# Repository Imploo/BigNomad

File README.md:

# BigNomad Keyboard

The BigNomad is a 9×5 keys, column-staggered split keyboard based largely on the [Nomad Keyboard](https://github.com/fiendie/NomadKeyboard), which is based on the [Sofle Choc by Brian Low](https://github.com/brianlow/SofleKeyboard).
It uses low profile Kailh Choc v1 switches with hotswap sockets and features per-key RGB lighting via SK6812 Mini-E LEDs.
Compared to the Nomad Keyboard the BigNomad offers an additional numpad as inner columns, an extra thumb cluster key, and an additional modifier key in the 5th row.
To make the keyboard more compact, support for OLED or pro micro based mcus are dropped. Instead, the mcu must be a RP2040 mini. Added support for a rotary encoder on top of the mcu footprint as well.

## RGB setup
I wanted to be able to control all leds individually on both hands, which is not possible when synching state through a serial connection. So I connected the last led to the trrs jack. All leds can then be chained in one long chain and all leds can be individually addressed. If you don't want this behaviour, choose jumper mcu on both halves. 

One caveat with using a trrs jack this way is that the serial connection is limited to half duplex serial. No full duplex or i2c possible. But since its not neccesary to sync the led state to the slave, the half duplex serial is fast enough.

## Bill of materials
- 2x RP2040 mini
- 6x female round header socket, the low profile ones that accept diode legs. They are break-apart into correct length, you need at least 46 pins.
- 2x EC11 rotary encoder
- 2x TRRS jack
- 1x TRRS cable
- 1x USB cable (pro tip; use the magnetic ones with data lines)
- 82x DIN123 diodes
- 82x SK6812 mini RGB leds
- 82x Kailh Choc hotswap sockets
- 82x Kailh Choc switches of your choice

## Build instructions
1. For the left hand side; Solder jumper J_RGB labeled mcu and keep trrs clear of any solder.
2. For the right hand side; choose whether you want to control the leds from the slave mcu or from the trrs plug. Solder the jumper mcu OR trrs. 
3. Solder diodes, keep an eye on the direction printed on the silk sheet.
4. Solder hotswap sockets
5. Solder RGBs
6. Solder encoder on the front side of the pcb.
7. Solder hotswap socket for mcu on the back side of the pcb. 
8. Solder pins on mcu
9. Place mcu, keep in mind the pin labeled as vcc!
10. Flash mcu and check workings of the RGB
11. Place a switch in a socket and test the matrix
12. Build the right hand side and test everything
13. Connect the two halves with a trrs cable and test the complete matrix. 

## Firmware 

Nomad uses [QMK firmware](https://qmk.fm/)

## Default layout 

TODO

## Images
These are still the original Nomad images, BigNomad images are pending..

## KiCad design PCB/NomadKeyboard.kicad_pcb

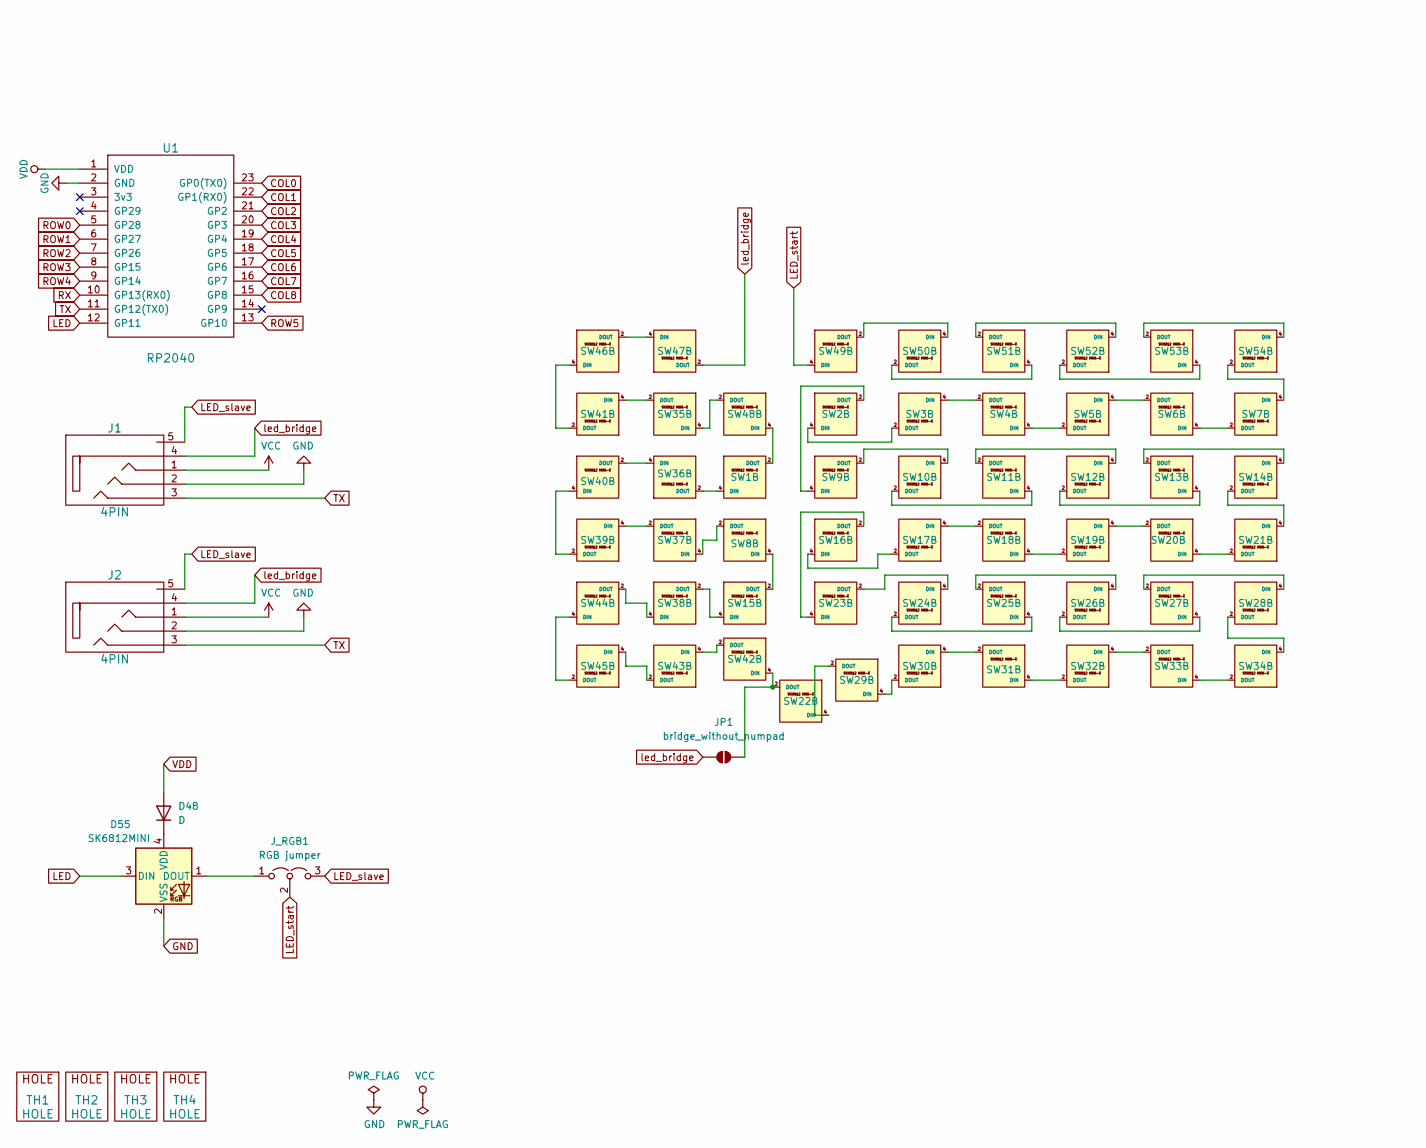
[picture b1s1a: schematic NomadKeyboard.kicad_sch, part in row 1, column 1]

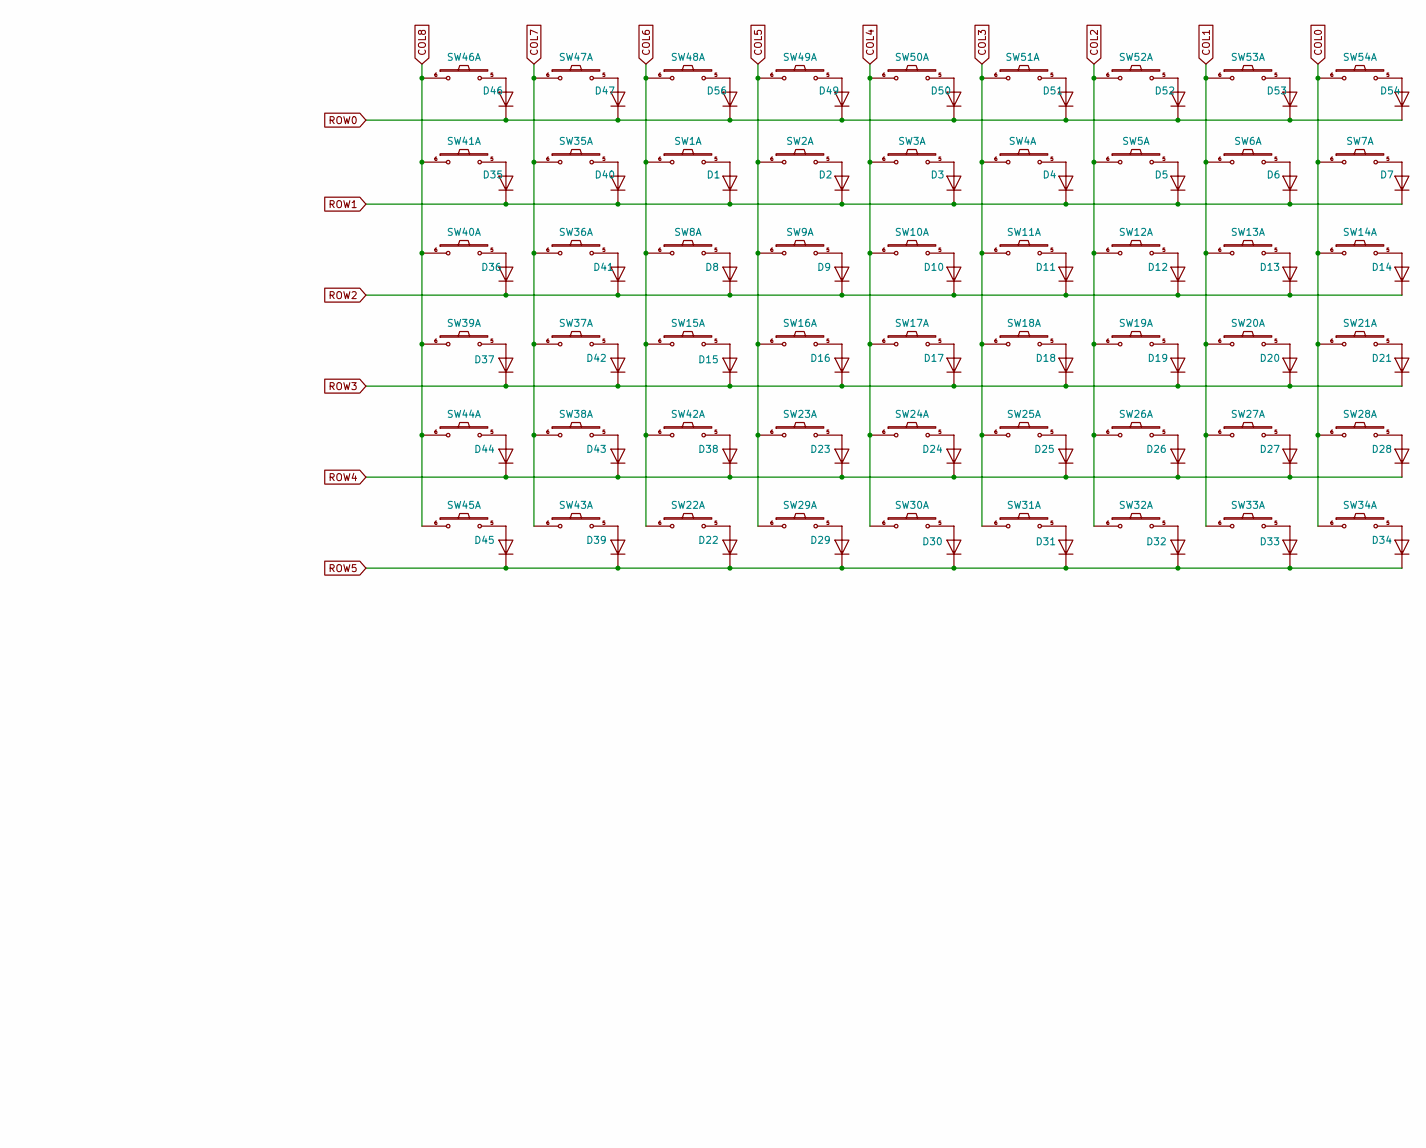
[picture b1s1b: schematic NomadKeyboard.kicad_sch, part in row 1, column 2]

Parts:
D1, D2, D3, D4, D5, D6, D7, D8, D9, D10, D11, D12, D13, D14, D15, D16, D17, D18, D19, D20, D21, D22, D23, D24, D25, D26, D27, D28, D29, D30, D31, D32, D33, D34, D35, D36, D37, D38, D39, D40, D41, D42, D43, D44, D45, D46, D47, D48, D49, D50, D51, D52, D53, D54, D56: D; crkbd-diode
D55: SK6812MINI; SK6812MiniE
J1, J2: 4PIN; MJ-4PP-9
JP1: bridge_without_numpad; SolderJumper-2_P1.3mm_Open_TrianglePad1.0x1.5mm
J_RGB1: RGB jumper; SolderJumper-3_P2.0mm_Open_TrianglePad1.0x1.5mm
SW1, SW2, SW3, SW4, SW5, SW6, SW7, SW8, SW9, SW10, SW11, SW12, SW13, SW14, SW15, SW16, SW17, SW18, SW19, SW20, SW21, SW22, SW23, SW24, SW25, SW26, SW27, SW28, SW29, SW30, SW31, SW32, SW33, SW34, SW35, SW36, SW37, SW38, SW39, SW40, SW41, SW42, SW43, SW44, SW45, SW46, SW47, SW48, SW49, SW50, SW51, SW52, SW53, SW54: SW_PUSH_LED; Choc_Hotswap_SK6812MiniE
TH1, TH2, TH3, TH4: HOLE; HOLE_M2_TH
U1: RP2040; rp2040-zero-smd

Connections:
COL0: SW7.6, SW14.6, SW21.6, SW28.6, SW34.6, SW54.6, U1.23 (GP0(TX0)); also elsewhere on the board
COL1: SW6.6, SW13.6, SW20.6, SW27.6, SW33.6, SW53.6, U1.22 (GP1(RX0)); also elsewhere on the board
COL2: SW5.6, SW12.6, SW19.6, SW26.6, SW32.6, SW52.6, U1.21 (GP2); also elsewhere on the board
COL3: SW4.6, SW11.6, SW18.6, SW25.6, SW31.6, SW51.6, U1.20 (GP3); also elsewhere on the board
COL4: SW3.6, SW10.6, SW17.6, SW24.6, SW30.6, SW50.6, U1.19 (GP4); also elsewhere on the board
COL5: SW2.6, SW9.6, SW16.6, SW23.6, SW29.6, SW49.6, U1.18 (GP5); also elsewhere on the board
COL6: SW1.6, SW8.6, SW15.6, SW22.6, SW42.6, SW48.6, U1.17 (GP6); also elsewhere on the board
COL7: SW35.6, SW36.6, SW37.6, SW38.6, SW43.6, SW47.6, U1.16 (GP7); also elsewhere on the board
COL8: SW39.6, SW40.6, SW41.6, SW44.6, SW45.6, SW46.6, U1.15 (GP8); also elsewhere on the board
GND: D55.2 (VSS), J1.2, J2.2, SW1.3 (GND), SW2.3 (GND), SW3.3 (GND), SW4.3 (GND), SW5.3 (GND), SW6.3 (GND), SW7.3 (GND), SW8.3 (GND), SW9.3 (GND), SW10.3 (GND), SW11.3 (GND), SW12.3 (GND), SW13.3 (GND), SW14.3 (GND), SW15.3 (GND), SW16.3 (GND), SW17.3 (GND), SW18.3 (GND), SW19.3 (GND), SW20.3 (GND), SW21.3 (GND), SW22.3 (GND), SW23.3 (GND), SW24.3 (GND), SW25.3 (GND), SW26.3 (GND), SW27.3 (GND), SW28.3 (GND), SW29.3 (GND), SW30.3 (GND), SW31.3 (GND), SW32.3 (GND), SW33.3 (GND), SW34.3 (GND), SW35.3 (GND), SW36.3 (GND), SW37.3 (GND), SW38.3 (GND), SW39.3 (GND), SW40.3 (GND), SW41.3 (GND), SW42.3 (GND), SW43.3 (GND), SW44.3 (GND), SW45.3 (GND), SW46.3 (GND), SW47.3 (GND), SW48.3 (GND), SW49.3 (GND), SW50.3 (GND), SW51.3 (GND), SW52.3 (GND), SW53.3 (GND), SW54.3 (GND), U1.2 (GND); also elsewhere on the board
LED: D55.3 (DIN), U1.12 (GP11); also elsewhere on the board
LED_slave: J1.5, J2.5, J_RGB1.3 (B); also elsewhere on the board
LED_start: J_RGB1.2 (C), SW49.4 (DIN); also elsewhere on the board
unnamed: D1.2 (A), SW1.5
unnamed: D2.2 (A), SW2.5
unnamed: D3.2 (A), SW3.5
unnamed: D4.2 (A), SW4.5
unnamed: D5.2 (A), SW5.5
unnamed: D6.2 (A), SW6.5
unnamed: D7.2 (A), SW7.5
unnamed: D8.2 (A), SW8.5
unnamed: D9.2 (A), SW9.5
unnamed: D10.2 (A), SW10.5
unnamed: D11.2 (A), SW11.5
unnamed: D12.2 (A), SW12.5
unnamed: D13.2 (A), SW13.5
unnamed: D14.2 (A), SW14.5
unnamed: D15.2 (A), SW15.5
unnamed: D16.2 (A), SW16.5
unnamed: D17.2 (A), SW17.5
unnamed: D18.2 (A), SW18.5
unnamed: D19.2 (A), SW19.5
unnamed: D20.2 (A), SW20.5
unnamed: D21.2 (A), SW21.5
unnamed: D22.2 (A), SW22.5
unnamed: D23.2 (A), SW23.5
unnamed: D24.2 (A), SW24.5
unnamed: D25.2 (A), SW25.5
unnamed: D26.2 (A), SW26.5
unnamed: D27.2 (A), SW27.5
unnamed: D28.2 (A), SW28.5
unnamed: D29.2 (A), SW29.5
unnamed: D30.2 (A), SW30.5
unnamed: D31.2 (A), SW31.5
unnamed: D32.2 (A), SW32.5
unnamed: D33.2 (A), SW33.5
unnamed: D34.2 (A), SW34.5
unnamed: D35.2 (A), SW41.5
unnamed: D36.2 (A), SW40.5
unnamed: D37.2 (A), SW39.5
unnamed: D38.2 (A), SW42.5
unnamed: D39.2 (A), SW43.5
unnamed: D40.2 (A), SW35.5
unnamed: D41.2 (A), SW36.5
unnamed: D42.2 (A), SW37.5
unnamed: D43.2 (A), SW38.5
unnamed: D44.2 (A), SW44.5
unnamed: D45.2 (A), SW45.5
unnamed: D46.2 (A), SW46.5
unnamed: D47.2 (A), SW47.5
unnamed: D48.1 (K), D55.4 (VDD)
unnamed: D49.2 (A), SW49.5
unnamed: D50.2 (A), SW50.5
unnamed: D51.2 (A), SW51.5
unnamed: D52.2 (A), SW52.5
unnamed: D53.2 (A), SW53.5
unnamed: D54.2 (A), SW54.5
unnamed 67: D55.1 (DOUT), J_RGB1.1 (A); also elsewhere on the board
unnamed: D56.2 (A), SW48.5
unnamed: JP1.1 (A), SW22.2 (DOUT), SW42.4 (DIN)
unnamed: SW1.4 (DIN), SW36.2 (DOUT)
unnamed: SW1.2 (DOUT), SW48.4 (DIN)
unnamed: SW2.4 (DIN), SW3.2 (DOUT)
unnamed: SW2.2 (DOUT), SW9.4 (DIN)
unnamed: SW3.4 (DIN), SW4.2 (DOUT)
unnamed: SW4.4 (DIN), SW5.2 (DOUT)
unnamed: SW5.4 (DIN), SW6.2 (DOUT)
unnamed: SW6.4 (DIN), SW7.2 (DOUT)
unnamed: SW9.2 (DOUT), SW10.4 (DIN)
unnamed: SW10.2 (DOUT), SW11.4 (DIN)
unnamed: SW11.2 (DOUT), SW12.4 (DIN)
unnamed: SW12.2 (DOUT), SW13.4 (DIN)
unnamed: SW13.2 (DOUT), SW14.4 (DIN)
unnamed: SW14.2 (DOUT), SW21.4 (DIN)
unnamed: SW15.4 (DIN), SW38.2 (DOUT)
unnamed: SW8.4 (DIN), SW15.2 (DOUT)
unnamed: SW16.4 (DIN), SW17.2 (DOUT)
unnamed: SW16.2 (DOUT), SW23.4 (DIN)
unnamed: SW17.4 (DIN), SW18.2 (DOUT)
unnamed: SW18.4 (DIN), SW19.2 (DOUT)
unnamed: SW19.4 (DIN), SW20.2 (DOUT)
unnamed: SW20.4 (DIN), SW21.2 (DOUT)
unnamed: SW22.4 (DIN), SW29.2 (DOUT)
unnamed: SW23.2 (DOUT), SW24.4 (DIN)
unnamed: SW24.2 (DOUT), SW25.4 (DIN)
unnamed: SW25.2 (DOUT), SW26.4 (DIN)
unnamed: SW26.2 (DOUT), SW27.4 (DIN)
unnamed: SW27.2 (DOUT), SW28.4 (DIN)
unnamed: SW28.2 (DOUT), SW34.4 (DIN)
unnamed: SW29.4 (DIN), SW30.2 (DOUT)
unnamed: SW30.4 (DIN), SW31.2 (DOUT)
unnamed: SW31.4 (DIN), SW32.2 (DOUT)
unnamed: SW32.4 (DIN), SW33.2 (DOUT)
unnamed: SW33.4 (DIN), SW34.2 (DOUT)
unnamed: SW35.4 (DIN), SW48.2 (DOUT)
unnamed: SW35.2 (DOUT), SW41.4 (DIN)
unnamed: SW36.4 (DIN), SW40.2 (DOUT)
unnamed: SW8.2 (DOUT), SW37.4 (DIN)
unnamed: SW37.2 (DOUT), SW39.4 (DIN)
unnamed: SW38.4 (DIN), SW44.2 (DOUT)
unnamed: SW39.2 (DOUT), SW40.4 (DIN)
unnamed: SW41.2 (DOUT), SW46.4 (DIN)
unnamed: SW42.2 (DOUT), SW43.4 (DIN)
unnamed: SW43.2 (DOUT), SW45.4 (DIN)
unnamed: SW44.4 (DIN), SW45.2 (DOUT)
unnamed: SW46.2 (DOUT), SW47.4 (DIN)
unnamed: SW49.2 (DOUT), SW50.4 (DIN)
unnamed: SW50.2 (DOUT), SW51.4 (DIN)
unnamed: SW51.2 (DOUT), SW52.4 (DIN)
unnamed: SW52.2 (DOUT), SW53.4 (DIN)
unnamed: SW53.2 (DOUT), SW54.4 (DIN)
unnamed: SW7.4 (DIN), SW54.2 (DOUT)
ROW0: D46.1 (K), D47.1 (K), D49.1 (K), D50.1 (K), D51.1 (K), D52.1 (K), D53.1 (K), D54.1 (K), D56.1 (K), U1.5 (GP28); also elsewhere on the board
ROW1: D1.1 (K), D2.1 (K), D3.1 (K), D4.1 (K), D5.1 (K), D6.1 (K), D7.1 (K), D35.1 (K), D40.1 (K), U1.6 (GP27); also elsewhere on the board
ROW2: D8.1 (K), D9.1 (K), D10.1 (K), D11.1 (K), D12.1 (K), D13.1 (K), D14.1 (K), D36.1 (K), D41.1 (K), U1.7 (GP26); also elsewhere on the board
ROW3: D15.1 (K), D16.1 (K), D17.1 (K), D18.1 (K), D19.1 (K), D20.1 (K), D21.1 (K), D37.1 (K), D42.1 (K), U1.8 (GP15); also elsewhere on the board
ROW4: D23.1 (K), D24.1 (K), D25.1 (K), D26.1 (K), D27.1 (K), D28.1 (K), D38.1 (K), D43.1 (K), D44.1 (K), U1.9 (GP14); also elsewhere on the board
ROW5: D22.1 (K), D29.1 (K), D30.1 (K), D31.1 (K), D32.1 (K), D33.1 (K), D34.1 (K), D39.1 (K), D45.1 (K), U1.13 (GP10); also elsewhere on the board
RX: U1.10 (GP13(RX0)); also elsewhere on the board
TX: J1.3, J2.3, U1.11 (GP12(TX0)); also elsewhere on the board
VCC: J1.1, J2.1
VDD: D48.2 (A), SW1.1 (VDD), SW2.1 (VDD), SW3.1 (VDD), SW4.1 (VDD), SW5.1 (VDD), SW6.1 (VDD), SW7.1 (VDD), SW8.1 (VDD), SW9.1 (VDD), SW10.1 (VDD), SW11.1 (VDD), SW12.1 (VDD), SW13.1 (VDD), SW14.1 (VDD), SW15.1 (VDD), SW16.1 (VDD), SW17.1 (VDD), SW18.1 (VDD), SW19.1 (VDD), SW20.1 (VDD), SW21.1 (VDD), SW22.1 (VDD), SW23.1 (VDD), SW24.1 (VDD), SW25.1 (VDD), SW26.1 (VDD), SW27.1 (VDD), SW28.1 (VDD), SW29.1 (VDD), SW30.1 (VDD), SW31.1 (VDD), SW32.1 (VDD), SW33.1 (VDD), SW34.1 (VDD), SW35.1 (VDD), SW36.1 (VDD), SW37.1 (VDD), SW38.1 (VDD), SW39.1 (VDD), SW40.1 (VDD), SW41.1 (VDD), SW42.1 (VDD), SW43.1 (VDD), SW44.1 (VDD), SW45.1 (VDD), SW46.1 (VDD), SW47.1 (VDD), SW48.1 (VDD), SW49.1 (VDD), SW50.1 (VDD), SW51.1 (VDD), SW52.1 (VDD), SW53.1 (VDD), SW54.1 (VDD), U1.1 (VDD); also elsewhere on the board
led_bridge: J1.4, J2.4, JP1.2 (B), SW47.2 (DOUT)

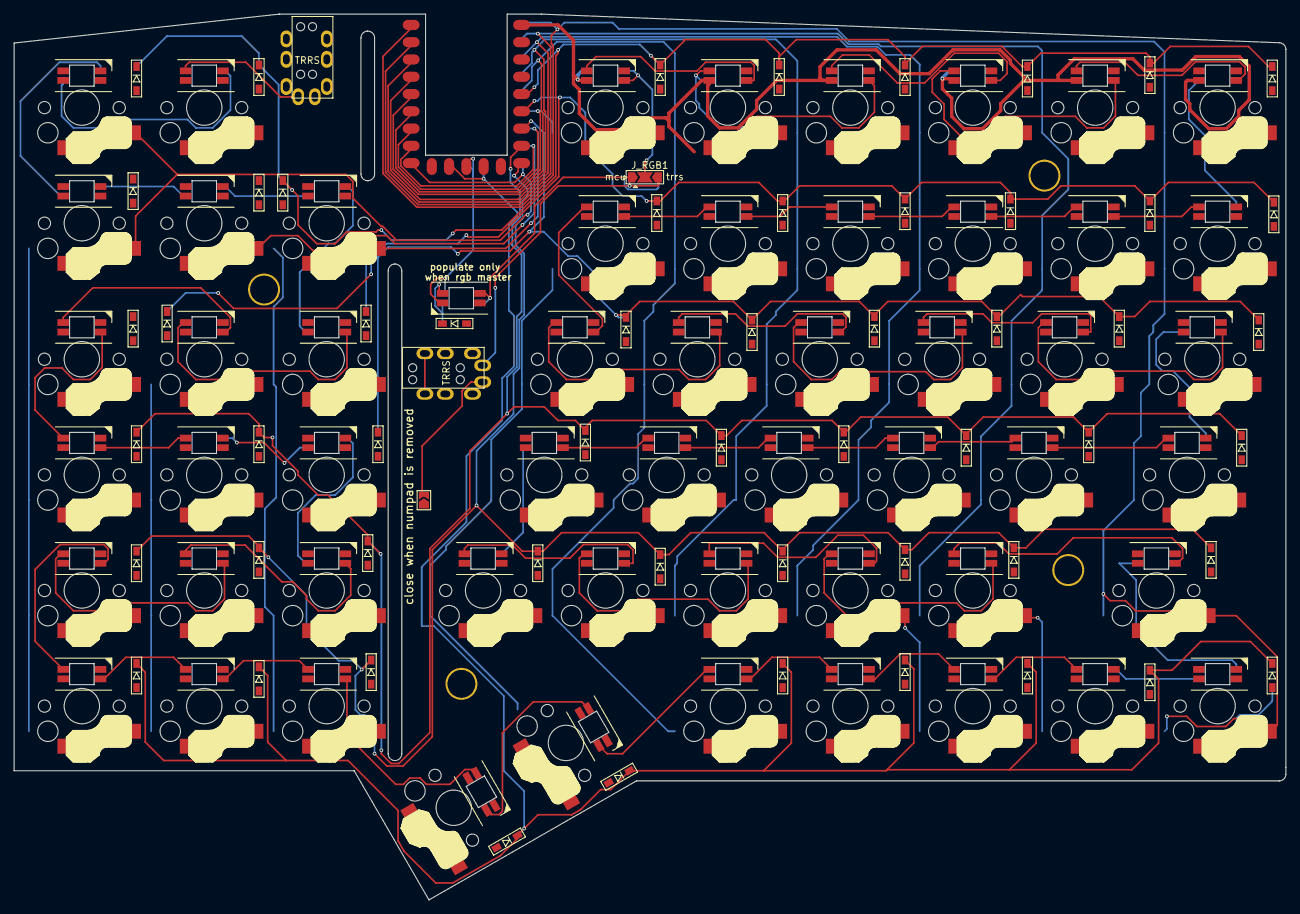
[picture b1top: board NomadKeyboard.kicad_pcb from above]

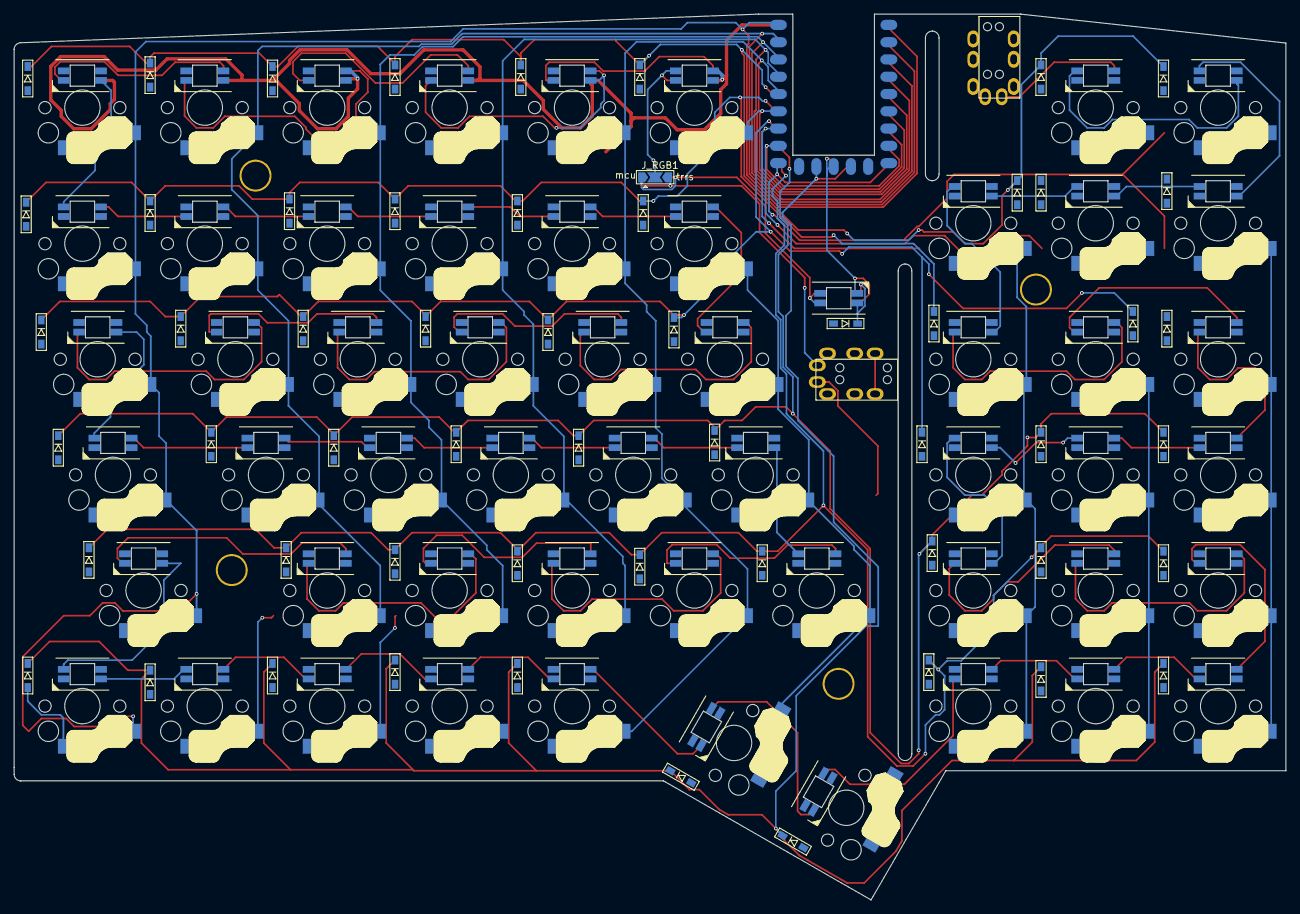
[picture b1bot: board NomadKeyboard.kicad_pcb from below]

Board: 2 copper layers, 187.0 x 130.2 mm, 121 parts (2 on the bottom side), 133 nets.

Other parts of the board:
J_RGB1#2: RGB jumper; SolderJumper-3_P2.0mm_Open_TrianglePad1.0x1.5mm
U1#2: RP2040; rp2040-zero-smd

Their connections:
COL0: U1#2.23 (GP0(TX0)); also elsewhere on the board
COL1: U1#2.22 (GP1(RX0)); also elsewhere on the board
COL2: U1#2.21 (GP2); also elsewhere on the board
COL3: U1#2.20 (GP3); also elsewhere on the board
COL4: U1#2.19 (GP4); also elsewhere on the board
COL5: U1#2.18 (GP5); also elsewhere on the board
COL6: U1#2.17 (GP6); also elsewhere on the board
COL7: U1#2.16 (GP7); also elsewhere on the board
COL8: U1#2.15 (GP8); also elsewhere on the board
GND: U1#2.2 (GND); also elsewhere on the board
LED: U1#2.12 (GP11); also elsewhere on the board
LED_slave: J_RGB1#2.3 (B); also elsewhere on the board
LED_start: J_RGB1#2.2 (C); also elsewhere on the board
unnamed 67: J_RGB1#2.1 (A); also elsewhere on the board
ROW0: U1#2.5 (GP28); also elsewhere on the board
ROW1: U1#2.6 (GP27); also elsewhere on the board
ROW2: U1#2.7 (GP26); also elsewhere on the board
ROW3: U1#2.8 (GP15); also elsewhere on the board
ROW4: U1#2.9 (GP14); also elsewhere on the board
ROW5: U1#2.13 (GP10); also elsewhere on the board
RX: U1#2.10 (GP13(RX0)); also elsewhere on the board
TX: U1#2.11 (GP12(TX0)); also elsewhere on the board
VDD: U1#2.1 (VDD); also elsewhere on the board

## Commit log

2024-10-22 added extra pins rp2040
2024-10-28 Revert "added extra pins rp2040"
    This reverts commit 3466adce22ebf42731cfeec9258051a6c0c8aed3.
2024-11-13 Added case
2024-11-16 row stagger layout
2024-11-20 before remove twosided feature
2024-11-20 after new layout
2024-11-23 new layout finished
2024-12-15 new case and fixed pinout
2024-12-22 last commit old case
2025-03-02 last stuff
2025-03-03 new design wip
2025-03-08 added rp2040
2025-03-11 last changes
